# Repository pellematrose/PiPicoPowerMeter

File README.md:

# PiPicoPowerMeter
Check out my project site at [hackaday.io](https://hackaday.io/project/189359-pi-pico-power-meter)

Use the latest Micropython release.
Copy the content of the "RP2040 Pi Pico Code_int_log" folder to the root directory of the RP2040.

## Configuration ##
The PPPM comes pre programmed ready to go to measure up to 26V and 3.2A.

If you need other / better performance on your measured object you can change the settings in the code.
Everything is done in this function:
```python
ina.configure(SHUNT_OHMS, VBUS_RANGE_16, VSHUNT_MAX_2, BADC_12BIT, SADC_12BIT, MODE_SHUNT_BUS_C)
```
Here's how to go:
1. Estimate your maximum voltage
	1. VBUS_RANGE_32 for max. 26V
	2. VBUS_RANGE_16 for max. 16V
2. Estimate the maximum current (with 0.1Ohms shunt) and set the gain
	1. VSHUNT_MAX_1 for range +-0.04mV -> Imax = 0.4A
	2. VSHUNT_MAX_2 for range +-0.08mV -> Imax = 0.8A
	3. VSHUNT_MAX_4 for range +-0.16mV -> Imax = 1.6A
	4. VSHUNT_MAX_8 for range +-0.32mV -> Imax = 3.2A
This will change the value of the LSB and thus change the precision.
The LSB is calculated like this: $LSB = \frac{maxcurrent}{2^{15}}$
If you soldered a different shunt the max. current changes to: $I=\frac{range}{shunt}$
3. Conversion speed (the faster the less accurate) Valid for BADC (Bus voltage)and SADC (Shunt voltage)
	1. BADC_9BIT for 9bit values in 84µs
	2. BADC_10BIT for 10bit values in 148µs
	3. BADC_11BIT for 11bit values in 276µs
	4. BADC_12BIT for 12bit values in 532µs
	5. BADC_2S for 2 Samples in 1.06ms
	6. BADC_4S for 4 Samples in 2.13ms
	7. BADC_8S for 8 Samples in 4.26ms
	8. BADC_16S for 16 Samples in 8.51ms
	9. BADC_32S for 32 Samples in 17.02ms
	10. BADC_64S for 64 Samples in 34.05ms
	11. BADC_128S for 128 Samples in 68.1ms
4. Choose the mode you need
	1. MODE_POWER_DOWN compleatly off
	2. MODE_SHUNT_TRIG only shunt, triggered
	3. MODE_VOLT_TRIG  only voltage, triggered
	4. MODE_SHUNT_BUS_T shunt and voltage, triggered
	5. MODE_ADC_OFF only adc off
	6. MODE_SHUNT_C only shunt, continuous
	7. MODE_VOLT_C only voltage, continuous
	8. MODE_SHUNT_BUS_C shunt and voltage, continuous

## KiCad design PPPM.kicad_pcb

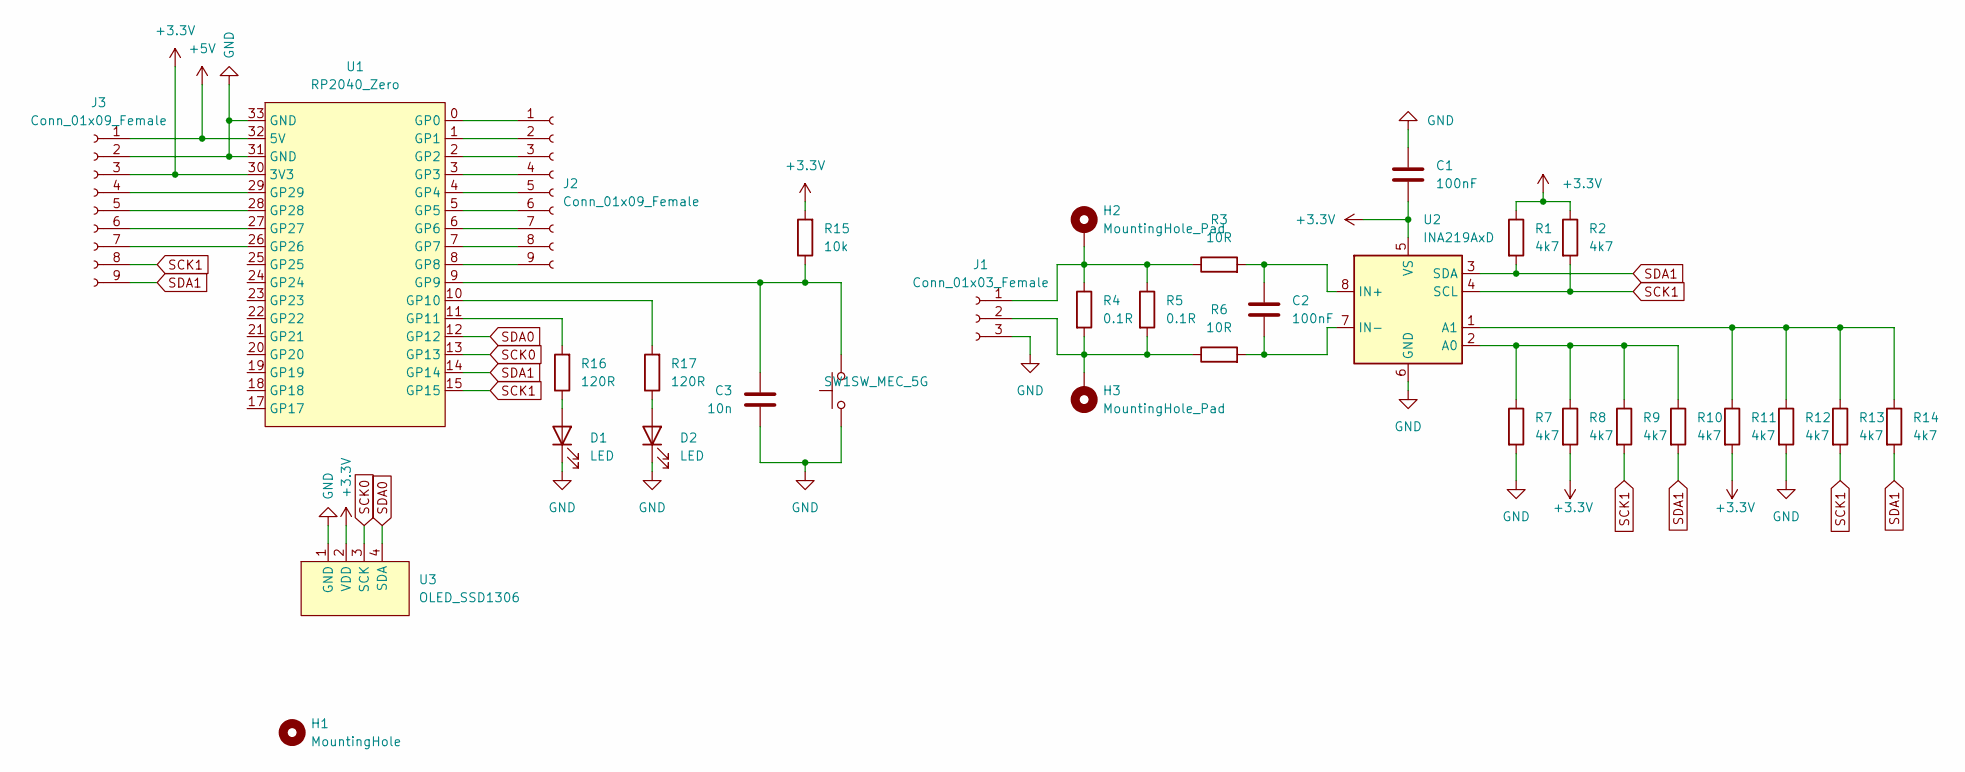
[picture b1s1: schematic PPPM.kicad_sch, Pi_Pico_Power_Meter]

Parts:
C1, C2: 100nF; C_0603_1608Metric_Pad1.08x0.95mm_HandSolder
C3: 10n; C_0603_1608Metric_Pad1.08x0.95mm_HandSolder
D1, D2: LED; LED_D5.0mm
H1: MountingHole; Langloch
H2, H3: MountingHole_Pad; MountingHole_3.2mm_M3_Pad_TopBottom
J1: Conn_01x03_Female; MKDS_3_3
J2, J3: Conn_01x09_Female; PinSocket_1x09_P2.54mm_Vertical
R1, R2, R7, R8, R9, R10, R11, R12, R13, R14: 4k7; R_0603_1608Metric_Pad0.98x0.95mm_HandSolder
R3, R6: 10R; R_0603_1608Metric_Pad0.98x0.95mm_HandSolder
R4, R5: 0.1R; R_2512_6332Metric_Pad1.40x3.35mm_HandSolder
R15: 10k; R_0603_1608Metric_Pad0.98x0.95mm_HandSolder
R16, R17: 120R; R_0603_1608Metric_Pad0.98x0.95mm_HandSolder
SW1: SW_MEC_5G; SW_Push_1P1T_NO_6x6mm_H9.5mm
U1: RP2040_Zero; RP2040-Zero
U2: INA219AxD; SOIC-8_3.9x4.9mm_P1.27mm
U3: OLED_SSD1306; SSD1306_0.96_Oled

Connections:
+3V3: C1.2, J3.3, R1.1, R2.1, R8.2, R11.2, R15.2, U1.30 (3V3), U2.5 (VS), U3.2 (VDD)
+5V: J3.1, U1.32 (5V)
GND: C1.1, C3.1, D1.1 (K), D2.1 (K), J1.3, J3.2, R7.2, R12.2, SW1.1 (A), U1.31 (GND), U1.33 (GND), U2.6 (GND), U3.1 (GND)
unnamed: C2.1, R3.2, U2.8 (IN+)
unnamed: C2.2, R6.2, U2.7 (IN-)
unnamed: C3.2, R15.1, SW1.2 (B), U1.9 (GP9)
unnamed: D1.2 (A), R16.1
unnamed: D2.2 (A), R17.1
unnamed: H2.1, J1.1, R3.1, R4.1, R5.1
unnamed: H3.1, J1.2, R4.2, R5.2, R6.1
unnamed: J2.1, U1.0 (GP0)
unnamed: J2.2, U1.1 (GP1)
unnamed: J2.3, U1.2 (GP2)
unnamed: J2.4, U1.3 (GP3)
unnamed: J2.5, U1.4 (GP4)
unnamed: J2.6, U1.5 (GP5)
unnamed: J2.7, U1.6 (GP6)
unnamed: J2.8, U1.7 (GP7)
unnamed: J2.9, U1.8 (GP8)
unnamed: J3.4, U1.29 (GP29)
unnamed: J3.5, U1.28 (GP28)
unnamed: J3.6, U1.27 (GP27)
unnamed: J3.7, U1.26 (GP26)
unnamed: R7.1, R8.1, R9.1, R10.1, U2.2 (A0)
unnamed: R11.1, R12.1, R13.1, R14.1, U2.1 (A1)
unnamed: R16.2, U1.11 (GP11)
unnamed: R17.2, U1.10 (GP10)
SCK0: U1.13 (GP13), U3.3 (SCK)
SCK1: J3.8, R2.2, R9.2, R13.2, U1.15 (GP15), U2.4 (SCL)
SDA0: U1.12 (GP12), U3.4 (SDA)
SDA1: J3.9, R1.2, R10.2, R14.2, U1.14 (GP14), U2.3 (SDA)

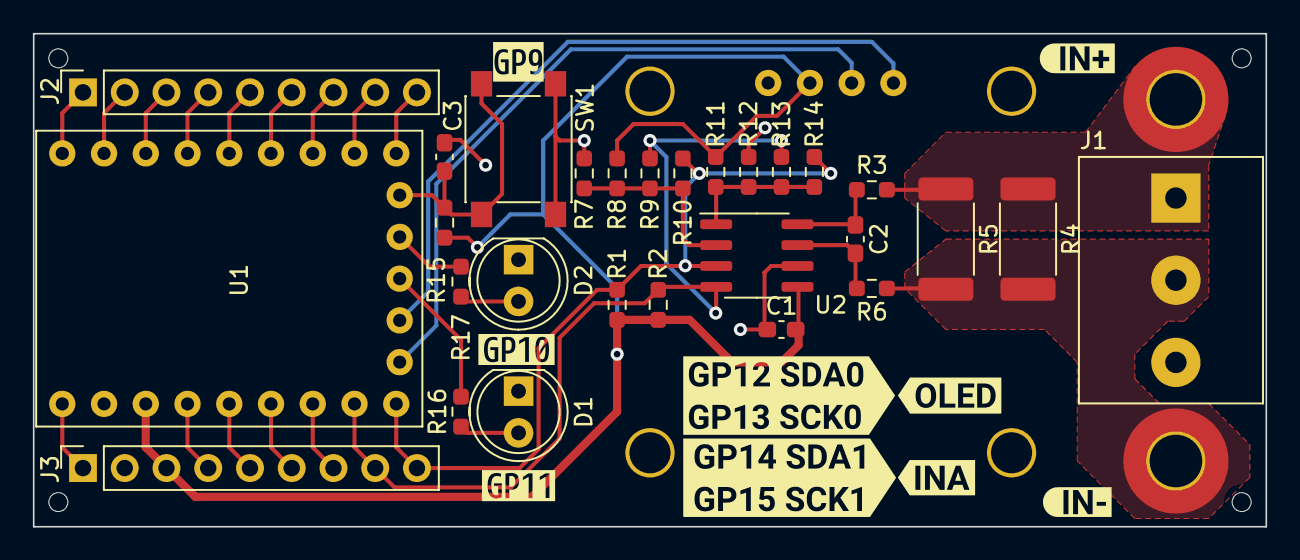
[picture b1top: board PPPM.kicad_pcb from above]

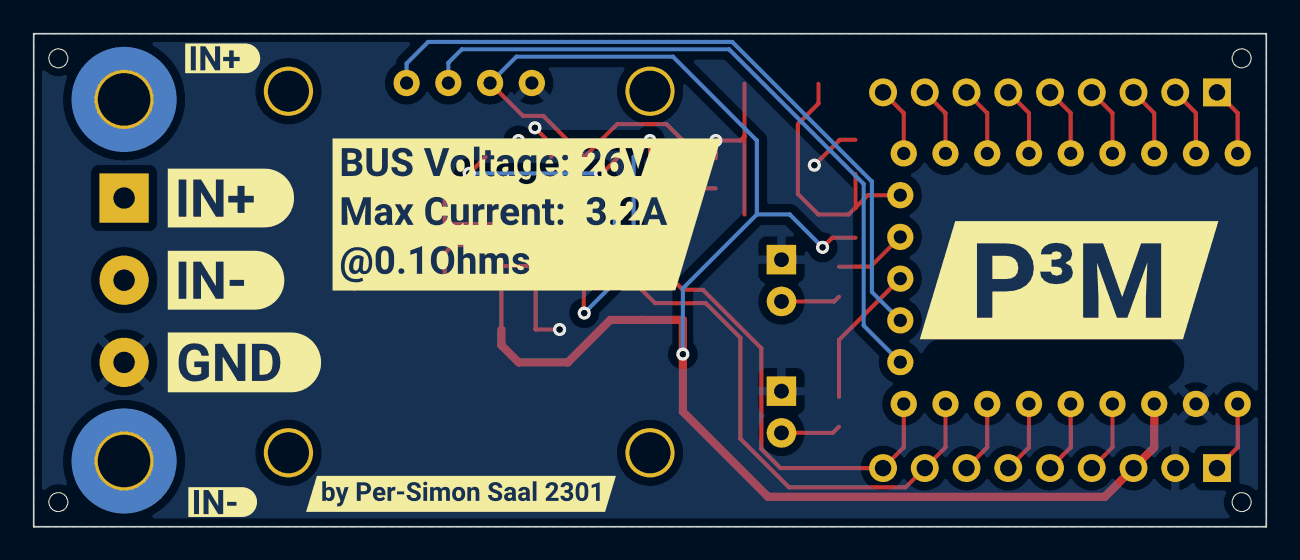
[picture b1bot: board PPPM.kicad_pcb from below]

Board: 2 copper layers, 75.0 x 30.0 mm, 53 parts (8 on the bottom side), 31 nets.

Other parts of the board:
MH*: Mounting_Hole_JLC
MH*#2, MH*#3, MH*#4: Mounting_Hole_JLC
kibuzzard-63CBEDF8: G***; kibuzzard-63CBEDF8
kibuzzard-63CBEE3D: G***; kibuzzard-63CBEE3D
kibuzzard-63CBEE36: G***; kibuzzard-63CBEE36
kibuzzard-63CBEF03: G***; kibuzzard-63CBEF03
kibuzzard-63CBF098: G***; kibuzzard-63CBF098
kibuzzard-63CC52B4: G***; kibuzzard-63CC52B4
kibuzzard-63CC52C8: G***; kibuzzard-63CC52C8
kibuzzard-63CC52D2: G***; kibuzzard-63CC52D2
kibuzzard-63CC54E8: G***; kibuzzard-63CC54E8
kibuzzard-63CC531B: G***; kibuzzard-63CC531B
kibuzzard-63CC537E: G***; kibuzzard-63CC537E
kibuzzard-63CC555B: G***; kibuzzard-63CC555B
kibuzzard-63CC555F: G***; kibuzzard-63CC555F
kibuzzard-63CC5329: G***; kibuzzard-63CC5329
kibuzzard-63CC5385: G***; kibuzzard-63CC5385
kibuzzard-63CC5526: G***; kibuzzard-63CC5526
kibuzzard-63CEA8C5: G***; kibuzzard-63CEA8C5

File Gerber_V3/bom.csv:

Designator,Footprint,Quantity,Value,LCSC Part #
"C1, C2",0603,2,100nF,
C3,0603,1,10n,
"D1, D2",LED_D5.0mm,2,LED,
"D3, D4",D_SMB,2,SM6T27A,
J1,MKDS_3_3,1,Conn_01x03_Female,
"J2, J3",PinSocket_1x09_P2.54mm_Vertical,2,Conn_01x09_Female,
"J4, J5",PinHeader_1x09_P2.54mm_Vertical,2,Conn_01x09_Female,
"R1, R10, R11, R12, R13, R14, R2, R7, R8, R9",0603,10,4k7,
R15,0603,1,10k,
"R16, R17",0603,2,120R,
"R3, R6",0603,2,10R,
"R4, R5",2512,2,0.1R,
SW1,SW_Push_1P1T_NO_6x6mm_H9.5mm,1,SW_MEC_5G,
U1,RP2040-Zero_SMD,1,RP2040_Zero,
U2,SOIC-8_3.9x4.9mm_P1.27mm,1,INA219AxD,
U3,SSD1306_0.96_Oled_wo_Holes,1,OLED_SSD1306,

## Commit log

2023-08-11 Data V3
2023-08-11 Add Schematic pdf
2024-08-28 Update main.py
    code cleanup, support for mili volts, amps, watts
2024-08-29 Update main.py
    Added two more buttons, different sample times for oled, measurement and csv, code cleanup
2024-08-30 Create functions.py
    externalise the functions to another file
2024-08-30 Update main.py
    moved functions to functions.py
2024-09-02 Update main.py
    added start_screen()
2024-09-02 Update functions.py
    added start_screen()
